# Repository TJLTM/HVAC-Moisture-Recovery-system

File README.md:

# HVAC-Moisture-Recovery-system
a split from my campkeen stuff just for galvanic sensors and tank level monitoring 

there is a caveaut for this in that the inputs are not optically isolated and bad things can occur under the right circumstances. 

King Of The Hill S04E22 Flush With Power

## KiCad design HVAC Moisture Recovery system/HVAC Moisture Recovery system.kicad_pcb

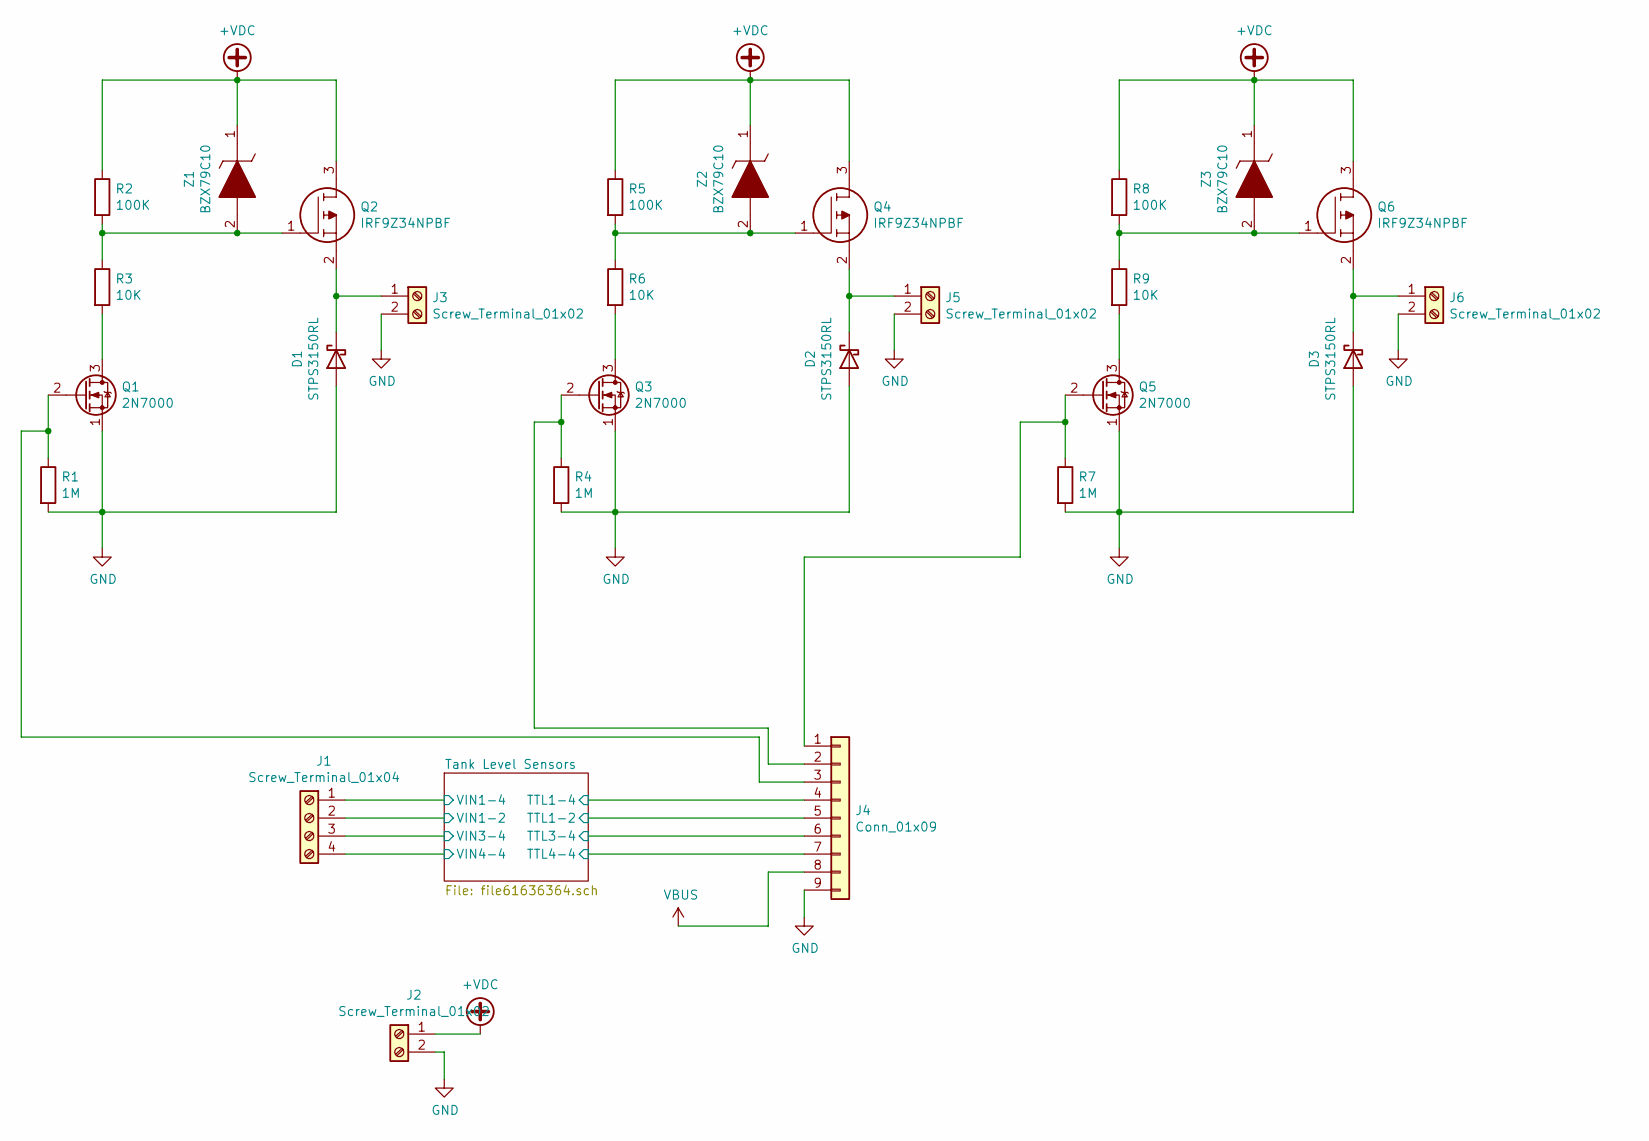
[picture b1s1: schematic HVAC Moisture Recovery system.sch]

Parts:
D1, D2, D3: STPS3150RL; D_DO-201_P15.24mm_Horizontal
J1: Screw_Terminal_01x04; TerminalBlock_Phoenix_MKDS-1,5-4-5.08_1x04_P5.08mm_Horizont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
J2, J3, J5, J6: Screw_Terminal_01x02; TerminalBlock_Phoenix_MKDS-1,5-2-5.08_1x02_P5.08mm_Horizont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
J4: Conn_01x09; PinHeader_1x09_P2.54mm_Vertical
Q1, Q3, Q5: 2N7000; TO-92_Inline
Q2, Q4, Q6: IRF9Z34NPBF; TO254P469X1042X1967-3P; Mouser Part Number 942-IRF9Z34NPBF
R1, R4, R7: 1M; R_Axial_DIN0204_L3.6mm_D1.6mm_P2.54mm_Vertical
R2, R5, R8: 100K; R_Axial_DIN0204_L3.6mm_D1.6mm_P2.54mm_Vertical
R3, R6, R9: 10K; R_Axial_DIN0204_L3.6mm_D1.6mm_P2.54mm_Vertical
Z1, Z2, Z3: BZX79C10; DIOAD1068W53L380D172; Mouser Part Number 512-BZX79C10

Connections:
+VDC: J2.1, Q2.3, Q4.3, Q6.3, R2.1, R5.1, R8.1, Z1.1, Z2.1, Z3.1
/Tank Level Sensors/TTL1-2: J4.5; also elsewhere on the board
/Tank Level Sensors/TTL1-4: J4.4; also elsewhere on the board
/Tank Level Sensors/TTL3-4: J4.6; also elsewhere on the board
/Tank Level Sensors/TTL4-4: J4.7; also elsewhere on the board
/Tank Level Sensors/VIN1-2: J1.2; also elsewhere on the board
/Tank Level Sensors/VIN1-4: J1.1; also elsewhere on the board
/Tank Level Sensors/VIN3-4: J1.3; also elsewhere on the board
/Tank Level Sensors/VIN4-4: J1.4; also elsewhere on the board
GND: D1.2 (A), D2.2 (A), D3.2 (A), J2.2, J3.2, J4.9, J5.2, J6.2, Q1.1 (S), Q3.1 (S), Q5.1 (S), R1.2, R4.2, R7.2; also elsewhere on the board
unnamed: D1.1 (K), J3.1, Q2.2
unnamed: D2.1 (K), J5.1, Q4.2
unnamed: D3.1 (K), J6.1, Q6.2
unnamed: J4.1, Q5.2 (G), R7.1
unnamed: J4.2, Q3.2 (G), R4.1
unnamed: J4.3, Q1.2 (G), R1.1
unnamed: Q1.3 (D), R3.2
unnamed: Q2.1, R2.2, R3.1, Z1.2
unnamed: Q3.3 (D), R6.2
unnamed: Q4.1, R5.2, R6.1, Z2.2
unnamed: Q5.3 (D), R9.2
unnamed: Q6.1, R8.2, R9.1, Z3.2
VBUS: J4.8; also elsewhere on the board

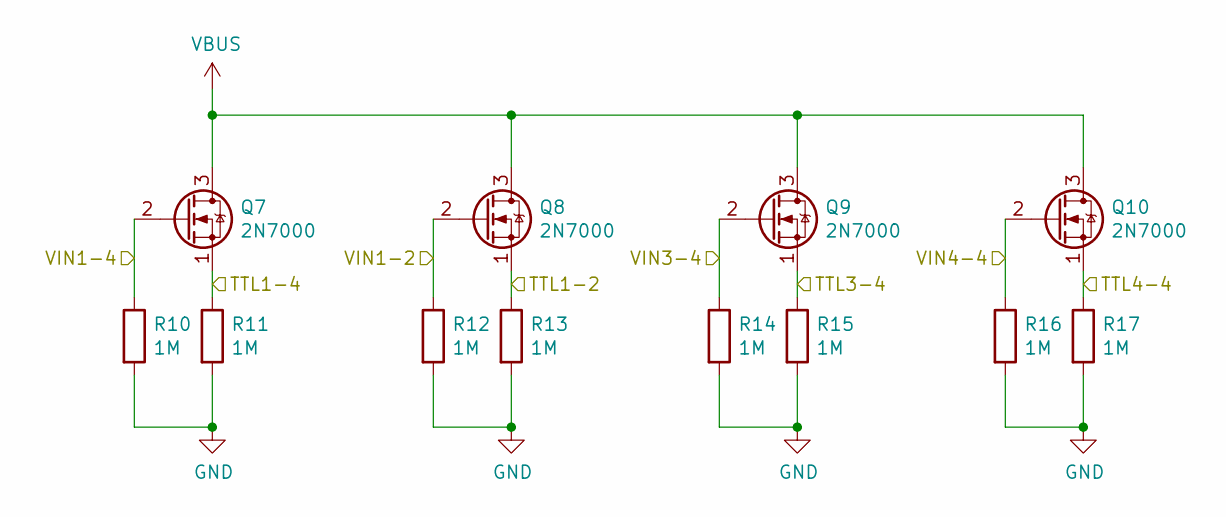
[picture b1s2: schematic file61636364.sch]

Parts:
Q7, Q8, Q9, Q10: 2N7000; TO-92_Inline
R10, R11, R12, R13, R14, R15, R16, R17: 1M; R_Axial_DIN0204_L3.6mm_D1.6mm_P2.54mm_Vertical

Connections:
/Tank Level Sensors/TTL1-2: Q8.1 (S), R13.1; also elsewhere on the board
/Tank Level Sensors/TTL1-4: Q7.1 (S), R11.1; also elsewhere on the board
/Tank Level Sensors/TTL3-4: Q9.1 (S), R15.1; also elsewhere on the board
/Tank Level Sensors/TTL4-4: Q10.1 (S), R17.1; also elsewhere on the board
/Tank Level Sensors/VIN1-2: Q8.2 (G), R12.1; also elsewhere on the board
/Tank Level Sensors/VIN1-4: Q7.2 (G), R10.1; also elsewhere on the board
/Tank Level Sensors/VIN3-4: Q9.2 (G), R14.1; also elsewhere on the board
/Tank Level Sensors/VIN4-4: Q10.2 (G), R16.1; also elsewhere on the board
GND: R10.2, R11.2, R12.2, R13.2, R14.2, R15.2, R16.2, R17.2; also elsewhere on the board
VBUS: Q7.3 (D), Q8.3 (D), Q9.3 (D), Q10.3 (D); also elsewhere on the board

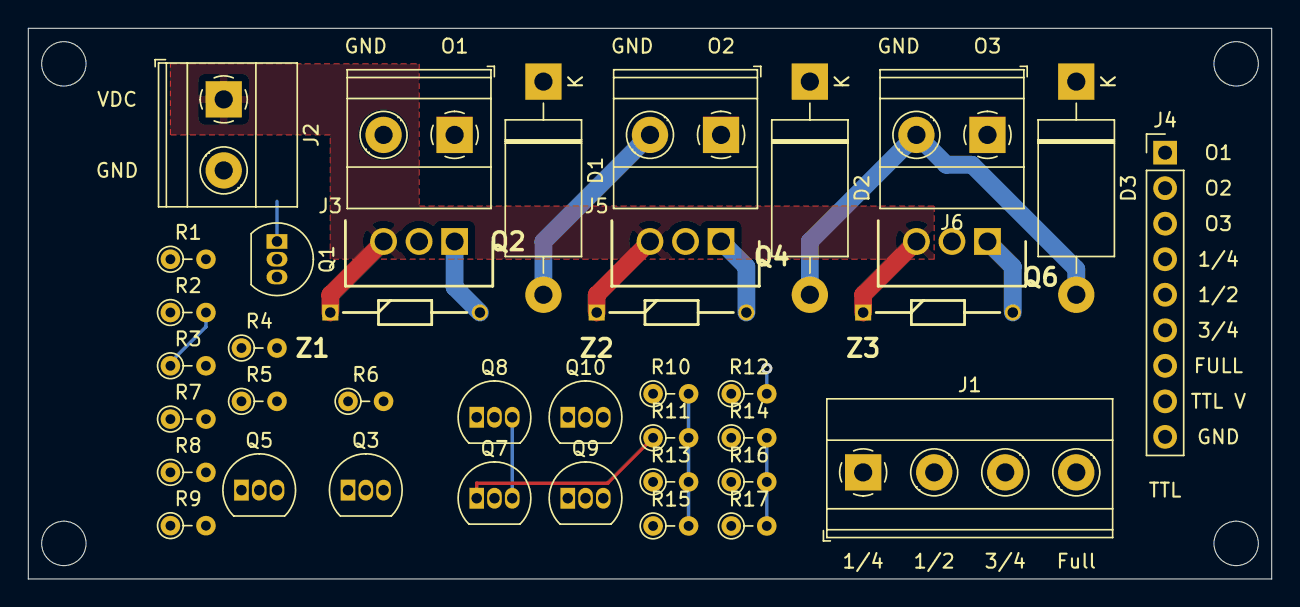
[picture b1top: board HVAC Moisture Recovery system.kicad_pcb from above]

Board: 4 copper layers, 88.9 x 39.4 mm, 39 parts (0 on the bottom side), 23 nets.

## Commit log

2021-10-10 initial and ready to fab
2021-11-02 HW verification sketch.
2021-11-03 updated code to fix how it actually works.
2021-11-19 Create LICENSE
